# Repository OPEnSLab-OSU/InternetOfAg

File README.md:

# Project Loom: Library Overview

This is the primary location of the Project Loom code, consolidated into place with a single Arduino .ino sketch built with code selected by the preprocessor based on the configuration file. 

Other readmes are provided for more specific content, while this document focuses on providing an overview of what Loom is and how the library works.

#### Additional Readmes

- [Arduino and Loom Setup](https://github.com/OPEnSLab-OSU/InternetOfAg/tree/master/Arduino_and_Loom_Setup) – How to setup Arduino and Loom from scratch
- [Hardware](https://github.com/OPEnSLab-OSU/InternetOfAg/blob/master/Readme_Hardware.md) – The processors, sensors, actuators, etc. that Loom uses / supports 
- [Using Loom](https://github.com/OPEnSLab-OSU/InternetOfAg/blob/master/ReadMe_Using_Loom.md) – How to use Loom once you have set it and the Arduino IDE up
- [Extending Loom](https://github.com/OPEnSLab-OSU/InternetOfAg/blob/master/ReadMe_Extending_Loom.md) – How to add support to the Loom Library
- [Hub Scripts](https://github.com/OPEnSLab-OSU/InternetOfAg/blob/master/ReadMe_Hub_Scripts.md) – Documentation on the mini programs / scripts that Loom supports
- [Loom Translator](https://github.com/OPEnSLab-OSU/InternetOfAg/blob/master/ReadMe_Loom_Translator.md) – Documentation on the collection of Loom functions for converting between data types and organization
- [Max MSP](https://github.com/OPEnSLab-OSU/Loom-Max) – Details on using Max MSP data processors with WiFi enabled Loom devices
- [Limitations and Bugs](https://github.com/OPEnSLab-OSU/InternetOfAg/blob/master/Readme_Limitations_and_Bugs.md) – The processors, sensors, actuators, etc. that Loom uses / supports 

## Table of Contents

1. [Installation](#installation)

2. [Device Support](#device-support)

3. [Communication Platforms](#communication-platforms)

    1. [Notes on Internet Connectivity](#notes-on-internet-connectivity)

4. [Device Configuration](#device-configuration)

5. [Max/MSP](#max/msp)

6. [Library Architecture](#library-architecture)

    1. [Overall Structure](#overall-structure)
        1. [Example Library Include Hierarchy](#example-library-include-hierarchy)

7. [Channels](#channels)
    1. [Implementation](#implementation)
    2. [Additional Devices](#additional-devices)

8. [Device Identification Hierarchy](#device-identification-hierarchy)

9. [SD Card Support](#sd-card-support)

10. [Real-Time Clock Support](#real-time-clock-support)

11. [Non-Volatile Flash and EEPROM memory](#non-volatile-memory)

12. [Configuration File](#configuration-file)

13. [API](#api)

14. [Using the Loom Library](#using-the-loom-library)

## Installation

See our [Arduino and Loom Setup Guide](https://github.com/OPEnSLab-OSU/InternetOfAg/tree/master/Arduino_and_Loom_Setup)

## Device Support

- Adafruit Feather M0
- Adafruit Feather 32u4 *(limited support)*

## Communication Platforms

WiFi and LoRa have had the most attention in development and thus have the most support and options, especially WiFi, as that is currently the only to communicate with a computer running Max/MSP. Other platforms have been implemented however. Below is the table of device inputs and outputs currently implemented, planned, or in consideration (bold for well implemented, * if partially implemented or in need of testing to be considered well implemented, plaintext if planned but not implemented, ? if in consideration). The top section is device-device communication platforms, and the bottom section are platforms that do not necessarily transmit directly to another Loom device

| Inputs         | Outputs                     | Comments                                                     |
| -------------- | --------------------------- | ------------------------------------------------------------ |
| **WiFi**       | **WiFi**                    | Implemented                                                  |
| **LoRa**       | **LoRa**                    | Implemented                                                  |
| **nRF**        | **nRF**                     | Implemented                                                  |
| Ethernet       | Ethernet*                   | Currently only used with hubs, expansion in progress         |
| GSM            | GSM*                        | Currently only one device, so outputs MQTT via GSM, but no GSM receiving yet |
|                |                             |                                                              |
| Google Sheets? | Google Sheets (PushingBox)* | Works as output                                              |
| Adafruit IO*   | Adafruit IO*                | Needs proper integration                                     |
| IFTTT?         | IFTTT?                      | IFTTT currently only works as output though Adafruit IO      |
| SD card?       | **SD card**                 | Works as output, considering as input                        |
| Serial?        | **Serial**                  | Works for output. Serial as input may or may not be useful (is how Fona is tested) |
|                | **OLED**                    | Display a bundle on an Adafruit OLED featherwing / breakout  |

### Notes on Internet Connectivity

**Ethernet MAC Addresses:** 

If you are not on a network where MAC addresses are managed / locked if not explicitly approved, then you will need obtain a valid MAC address from your IT department. Once you have a MAC address, it can be set in the code with something like `byte mac[] = {0x98, 0x76, 0xB6, 0x10, 0x61, 0xD6};` It would generally be worth testing a new MAC address in basic example code first to ensure that will in fact work.

**WiFi Network Connectivity:** 

Many institutional / company WiFi network require a user's credentials to be access (rather than just network SSID and password). We do not currently support connecting to such networks, and it is unclear if this can be implemented on Arduinos at all.

As such, you can operated the Loom WiFi device in:

- Access point mode without internet access
- Client mode connected to a WiFi router that does not connect to an institutional/ username protected network for internet access
- Client mode connected to a WiFi router unconnected to internet for local communication between devices but no internet access

## Device Configuration

The configuration of the code to upload and flash to devices is specified in the config.h file. This file presents the options that can be set or toggled to achieve a particular behavior. The preprocessor uses these definitions to select the necessary declarations, variables, and functions automatically. 

Currently changes to the config need to be done manually in the file itself. An interface to aid the process is in progress.

## Max/MSP

The associated [Loom Data Processors](https://github.com/OPEnSLab-OSU/Loom-Max) and control modules are made as patches in Max/MSP. The Max interfaces are not strictly necessary for using this library, but provide convenient features and means of interacting with your Loom devices / network.

## Librarary Architecture

The Loom Library is an answer to the growing set of code to drive Loom's supported devices, hardware, and communication platforms. The set of possible combinations of device configurations makes it unfeasable for Loom developers and users alike to manage sketches with desired functionality. Instead, a configuration file effectively creates the desired sketch dynamically. A loom_preamble.h file uses that configuration to select entire files to include, each of which may also contain additional preprocessor statements.

### Overall Structure

The Loom Library is effectively an aggregate of all of the functionality possible within the entirety of the supported devices, sensors, and actuators. The user then specifies the needs of their sketch inside the `config.h`. Based on the needs of the sketch, the requisite files, functions, and logic will be dynamically included such that only what is needed by the sketch is uploaded to the device. loom_preamble.h uses `config.h` to know which files to include, these files in turn then include the libraries they need. `loom_common.h` is also always present as it has the `Loom_begin()` function, which sets up all the modules and sensors being used by the sketch. 

#### Example Library Include Hierarchy

The hierarchy of included files looks something like the following (example if building for Ishield device on Feather M0 WiFi)  *(actual files may have since changed, but the idea/hierarchy remain)*. 

**Note** – bolded are files that are always necessary and thus included, independent of `config.h`. In angle brackets are non-Loom dependencies.

- Ishield_Example.ino
  - **Config.h**
  - **Loom_preamble.h** (likely to be renamed)
    - **<OSCBundle.h>**
    - Loom_translator.h
    - <Adafruit_SleepyDog.h>
    - <SPI.h>
    - loom_analog.h
    - loom_neopixel.h
      - <Adafruit_NeoPixel.h>
    - loom_mpu6050.h
      - <I2Cdev.h>
      - <Wire.h>
      - <MPU6050_6Axis_MotionApps20.h>
    - loom_wifi.h
      - <WiFi101.h>
      - <WiFiUDP.h>
    - **loom_flash.h**
      - <FlashStorage.h>
    - **loom_common.h**

### Message Router

#### Intro to Route and Dispatch of Message Router

The message router is called via:

```
bndl->route(configuration.packet_header_string, msg_router);
```

From the `process_bundle` function in the 'loom_interface.h' file. The message router checks any OSC messages that it receives, and if the message's address string matches one of the dispatch calls in the router, then the message gets forwarded to a function designed to handle / process messages with that address string. This usually entails reading the arguments to the message (which should be sent in an order / format known by the function that will handle the processing).

The dispatch calls in the message router take the following form:

```
msg.dispatch("/address", processing_function, addrOffset);
```

An example of a dispatch that takes a message that has an address of the device identifying string followed by "setID", and calls a function `set_instance_num` (which sets the device instance number) would be:

```
msg.dispatch("/SetID", set_instance_num, addrOffset);
```

The reason only the `/SetID` is provided and not something like `/LOOM/Ishield7/SetID` is because the aforementioned route function checks for message addressed to the device, which in this case is identified by `/LOOM/Ishield7`, and passes only the remaining part of the address to the message router. Messages that do not start with the device indentifying string are not sent to the message router.

## Channels

The LOOM library and associated Max/MSP processors are designed to use channel based interfaces by default. Channel interfaces abstract device instance number, UDP port, and IP address into a single letter A, B, C, … H. 

The channels are purely a user convenience, and the devices can operate without any notion of channels in the firmware and/or Max patches.

### Implementation
A common port is used for the communication of device settings in order to allow the Max patches to communicate with devices in a consistent manner if the instance number, UDP port, or IP (i.e. the channel information) address are unknown.

**Common Port:** 9440 

**Device Unique Channnel Data:** 9441 – 9448

Channel A:	Instance # = 1		UDP Port = 9441	

Channel B:	Instance # = 2		UDP Port = 9442

• • •

Channel H:	Instance # = 8		UDP Port = 9448

**IP Address:** Automatically assigned to devices by one's router. Max interfaces will automatically fetch IP address of selected device. If not using the channels feature implemented in the Loom Max interfaces, then Loom Debug mode may need to be enabled, or the user may need to add custom code, in order to obtain the device's IP address.

### Additional Devices

The Max interfaces presently support upto 8 concurrent channels, though the library itself poses no such restrictions and using custom Max interfaces can allow for the control of more devices.

## Device Identification Hierarchy

In Loom, a device is uniquely identified by 4 elements, from broad to precise identification:

- Family
- Family number
- Device type
- Device number

The OSC messages and bundles send to and from devices are address/signed with their ID string, in the following format:

`/<Family><Family-Num>/<Device-Type><Device-Num>/<the-rest-of-the-address>`

For example, Ishield 7 in the 3 'Loom' subnet would be:

`/Loom3/Ishield7`

**Family**

A family is generally a complete network of a given functionality under a single person or group.

**Family Number**

A family number is used to distinguish subnets between a family. This is typically used to seperate devices into groups by purpose, location, etc. In Max/MSP, you will generally only be observing a single subnet at a time. Family numbers should be 0 or greater.

**Device Type**

The Loom Library supports an autoname feature to try to name your device if it fits into a common hardware / functionality set. These include devices like Ishields, multiplexers, servo controllers, etc. and name the device accordingly. Alternatively, you can use custom names for your devices if you want. 

**Device Number / Channel**

A device number is used to distinguish the devices on the same subnet (family number) that have the same device type. Device numbers are sometimes also referred to as channels. Device numbers are expected to be between 1 and 8, inclusive (channels A-H).

### WiFi UDP Ports

If using WiFi, the family number and device number will determine the UDP ports that the device will expect messages from. The device will check and send on 3 ports, one for global messages, one for subnet, and one for device specific messages. The calculation of the specific ports are shown below. The reason for different ports fro various devices/purposes is to reduce the number of messages a device may recieve that were not intended for it.

### Device Targetting Scope

The message routing function of the Loom Library supports receiving messages addressed at a global, subnet, or device level. Max/MSP can send on any of the 3 formats as well.

**Global** 

Broadcast the OSC bundle to all devices. Those with the matching family name can see/react to the message. If using WiFi the message is sent on UDP port `9400`.

`/<Family>/<command>`

**Subnet**

Broadcast to a single subnet of a given family. Those with the matching family name and family number can see/react to the message. If using WiFi the message is sent on UDP port `9400+10*(family-num)`.

`/<Family><Family-Num>/<command>`

**Device**

Target a message at a single device, i.e. the one with the matching family, family number, device type, and device number. If using WiFi the message is sent on UDP port `9400+10*(family-num)+(device-num)`.

`/<Family><Family-Num>/<Device-Type><Device-Num>/<command`

### LoRa Subnet

Loom also supports subnets with LoRa. This is implemented by having the receiver check the source of the received OSC bundle (from the device identification address), and filter out unwanted bundles (i.e. empty them). 

The options are specified in the config.h file by `lora_subnet_scope`:

- 1: subnet
- 2: global/family
- 3: global only (not recommended)
- 4: any message. 

(use 2 if unsure)

These achieve a similar subnet structure that is produced with UDP ports on the WiFi boards.

## SD Card Support

The Loom library extends the Arduino SD library to have more features, mostly tailored towards using common data structures used by the library.

Namely, support for printing:

- Single elements (int, floats, c-strings, Strings)
- Arrays (ints, floats, c-strings, Strings)
- Bundles (single or multi-msg format)

Additionally, if used with MaxMSP, there is support for sending commands to enable / disable the logging of bundles the device receives (also works without Max).

## Real-Time Clock Support

The Loom library supports two RTC devices:

- [Adafruit DS3231](https://learn.adafruit.com/adafruit-ds3231-precision-rtc-breakout/)
- [Adafruit PCF8523](https://learn.adafruit.com/adafruit-adalogger-featherwing)

Currently, interrupts (for waking the microprocessor from sleep) are only supported via the DS3231, with the PCF8523 mostly being used in conjunction with an SD card (as Adafruit Adalogger featherwing has PCF8523 and SD card holder) to provide timestamps.

The Loom Library has support for both devices for returning strings of the date, time, or weekday. Additional timer functions are provided for the DS3231.

#### RTC and Low Power Dependencies

- [DS3231 Extended Library](https://github.com/FabioCuomo/FabioCuomo-DS3231)
- [Low Power Library](https://github.com/rocketscream/Low-Power)
- [Enable Interrupt](https://github.com/GreyGnome/EnableInterrupt)

**NOTE:** To use the DS3231 extended library with the Feather M0,
the following line must be added to `RTClibExtended.h`:

```cpp
#define _BV(bit) (1 << (bit))
```

#### Sleep Modes

Project Loom supports two sleep modes for the Feather M0 and one sleep mode for the Feather 32u4.
Here are some details on the various modes:

| Mode           | Supported board | Current Draw |
| -------------- | --------------- | ------------ |
| Idle\_2        | Feather M0      | ~5 mA        |
| Standby        | Feather M0      | ~0.7 mA      |
| SLEEP\_FOREVER | Feather 32U4    | Untested     |

#### Standby Operation

Due to some incompatibilities between Standby mode and falling interrupts, a very particular
scheme must be followed to use Standby mode on the Feather M0.  The following code is an
example of how standby mode can be set up on the M0 with a wakeup interrupt on pin 11:

``` cpp
void setup() {
    pinMode(11, INPUT_PULLUP);
    bool OperationFlag = false;
    delay(10000); //It's important to leave a delay so the board can more easily
                  //be reprogrammed
}

void loop() {
    if (OperationFlag) {

        // Whatever you want the board to do while awake goes here

        OperationFlag = false; //reset the flag
    }

    attachInterrupt(digitalPinToInterrupt(11), wake, LOW);

    LowPower.standby();
}

void wake() {
    OperationFlag = true;
    detachInterrupt(digitalPinToInterrupt(11)); //detach the interrupt in the ISR so that
                                                //multiple ISRs are not called
}
```

#### Setting the Time from the Internet

Loom supports setting the RTC time based on the time obtained from an NTP server.

#### UTC Time

Loom supports the usage of either local or UTC time.

## Non-Volatile Flash and EEPROM memory

For storing configurations, both the Feather M0 and the Feather 32u4 boards are capable of storing a
struct in non-volatile memory. The functions related to non-volatile memory can be found in loom_flash.h,
and are automatically compatible with your board. If you modify the contents of the configuration structure,
you can save them with write_non_volatile(). If you need to read from flash memory, you can read into the
configuration structure with read_non_volatile(). Do not excessively write, as each board supports about
~10000 flash writesin its lifetime; the cells in flash memory wear out over time.

## Configuration File

The configuration file is used in conjunction with preprocessor statements to build the specified sketch, with as small a program memory usage as possible. Any options that can be set or toggled, or any specification of hardware (e.g. sensors and actuators) being used occur in this config.h.

Any options for custom additions to the library should be added only to the configuration file.

The config.h file needs to be included before the library (via loom_preamble.h) itself, so that the configuration can be used to define the necessary subset of the library.

## API

*'[]'s are used to indicate arguments that are optional or specific to a given platform* 

- Receive Bundle `void receive_bundle(OSCBundle *bndl, CommPlatform platform)`
  - Receive a packet and put it in an OSC bundle if not already
  - CommPlatform options:
    - WIFI
    - LORA
    - NRF
- Process Bundle `void process_bundle(OSCBundle *bndl)`
  - Process a bundle (presumably recieved via recieve_bundle) by performing message routing on it 
- Measure Sensors `void measure_sensors()`
  - Measure any enabled sensors
- Package Data `void package_data(OSCBundle *send_bndl)`
  - Package measured data into an OSC bundle  
- Send Bundle `void send_bundle(OSCBundle *send_bndl, CommPlatform platform)` 
  - Send a bundle (presumably built via package_data) to another Loom device / MaxMSP
- Log Bundle `void log_bundle(OSCBundle *send_bndl, LogPlatform platform [,char* file])`
  - Export a bundle
  - Platform options
    - PUSHINGBOX (Google Sheets)
    - SDCARD (requires filename)
    - OLED
- Additional Loop Checks `void additional_loop_checks()`
  - Function to catch remaining functionality that is not contained by the rest of the API

Further details on using the API can be found [here](https://github.com/OPEnSLab-OSU/InternetOfAg/blob/master/ReadMe_Using_Loom.md)

## Using the Loom Library

Details on setting up Arduino IDE and Loom can be found [here](https://github.com/OPEnSLab-OSU/InternetOfAg/tree/master/Arduino_and_Loom_Setup)

Details on using Loom once setup (with examples) can be found [here](https://github.com/OPEnSLab-OSU/InternetOfAg/blob/master/ReadMe_Using_Loom.md)

####

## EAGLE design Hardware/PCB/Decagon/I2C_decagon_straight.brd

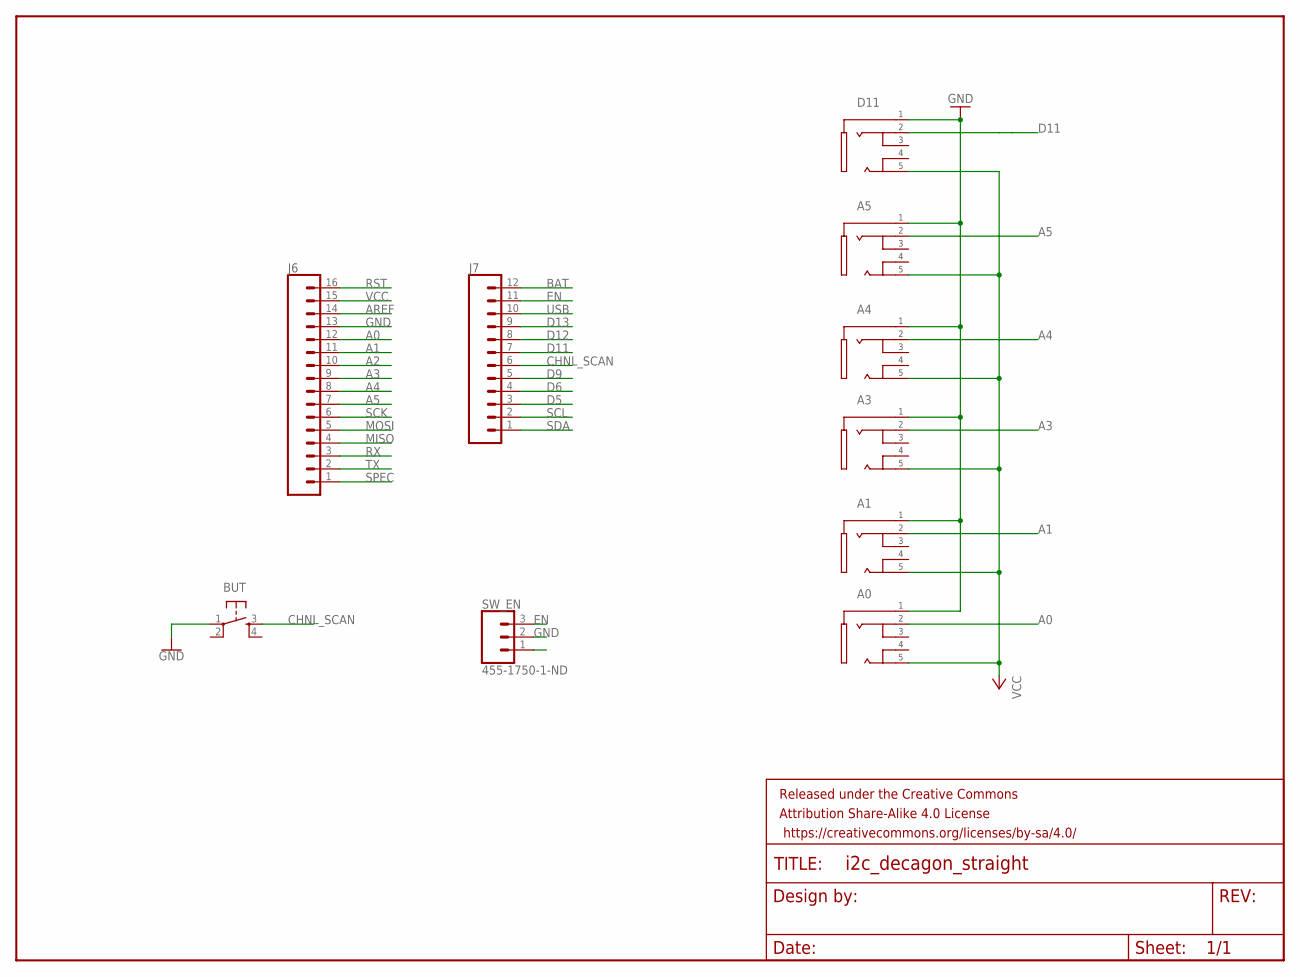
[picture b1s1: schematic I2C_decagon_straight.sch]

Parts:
A0, A1, A3, A4, A5: JW-PJ-307-5H
BUT: TAC_SWITCHPTH; TACTILE-PTH
D11: JW-PJ-307-5H
FRAME1: FRAME-LETTER; CREATIVE_COMMONS
J6: CONN_16; 1X16
J7: CONN_12; 1X12
SW_EN: 455-1750-1-ND; 1X03

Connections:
A0: A0.2, J6.12
A1: A1.2, J6.11
A2: J6.10
A3: A3.2, J6.9
A4: A4.2, J6.8
A5: A5.2, J6.7
AREF: J6.14
BAT: J7.12
CHNL_SCAN: BUT.3, J7.6
D5: J7.3
D6: J7.4
D9: J7.5
D11: D11.2, J7.7
D12: J7.8
D13: J7.9
EN: J7.11, SW_EN.3
GND: A0.1, A1.1, A3.1, A4.1, A5.1, BUT.1, D11.1, J6.13, SW_EN.2
MISO: J6.4
MOSI: J6.5
RST: J6.16
RX: J6.3
SCK: J6.6
SCL: J7.2
SDA: J7.1
SPEC: J6.1
TX: J6.2
USB: J7.10
VCC: A0.5, A1.5, A3.5, A4.5, A5.5, D11.5, J6.15

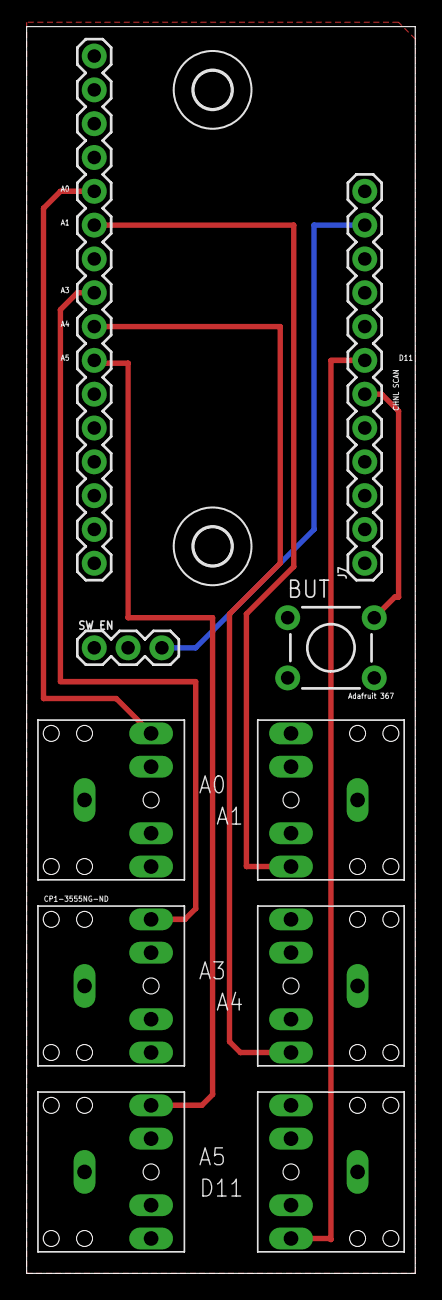
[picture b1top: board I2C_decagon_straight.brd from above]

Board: 2 copper layers, 29.2 x 93.7 mm, 13 parts (0 on the bottom side), 10 nets.

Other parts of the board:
U$1, U$2: 2,8

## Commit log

2017-11-29 Added Decagon soil moisture sensor demo
2017-11-30 Created subroutines for reading decagon values and sending OSC bundles
2018-01-17 Added Decagon functionality
2018-02-01 Added code to operate multiple decagon sensors
2018-02-07 Edited multiple decagon sensor code to be functional
2018-02-07 Changes for demo
2018-02-12 Modified OSC_interpret to account for messages with multiple data
2018-02-12 Added dynamic sensor polling on pins A0-A5
2018-02-16 Added sensor specific processing for GS3 and 5TM
2018-02-16 Added 32u4 compatibility
2018-02-16 32u4 changes
2018-02-22 Added 32u4 compatibility to nRF_OSCtransmit/receive
2018-02-28 Updated pins for 32u4 compatibility
2018-03-07 Interpretter revamp for multiple data values
2018-03-07 Servo code taking inputs in serial monitor
2018-03-07 OSCbundle+servo
    Applied OSCbundle library and etc to the servo code to use maxmsp
2018-03-10 Added PC application and LoRa OSC bundle send template
2018-03-10 Removed unnecessary library
2018-03-12 Quick receive edit for check off
2018-03-13 Added Decagon and Thermocouple code
2018-03-13 Added nRF code
2018-03-13 Added nRF thermocouple code
2018-03-13 Servo codes work with m0 and 32u4 through LoRa
    Servo_LoRa : Servo code
    LoRa_xransmit: transmitter code
2018-03-16 Added new files
2018-03-16 nrf data rate code added
2018-04-17 Code altered to allow larger bundles
2018-04-17 Readme update
2018-05-17 Removed RTC functionality for expo demo
2018-06-06 add static/dynamic i2c device configuration for mpu6050
2019-01-28 Fix Pushingbox readme to include tab ID in example format
2019-02-06 testing commitability
2019-02-06 Fixed archived libraries to be easier to use.
2019-02-15 Added turbidity conversion
2019-02-15 Restore .ino
2019-02-15 Added EC and TDS conversions
2019-02-22 Added Doxygen Make file for generating project documentation
2019-02-22 Readme edits
2019-02-22 Update dependencies folder
2019-02-27 Fix Ms5803 library to take i2c as parameter
2019-03-01 Minor Max31856 declaration rearrangement
2019-03-01 Remove old images folder
2019-03-01 Added BEE 222 instance
2019-03-22 New Decagon board
    Fixed order for snapping off unused ports. Change formfactor
2019-03-26 Fixed traces on Decagon 2.1
2019-04-01 Moved Traces clearance
2019-04-03 Traces shifted
    Modified 2.1 version to put more space between traces and soldering locations. Added silk screen text for relevant pins.
2019-05-03 Add Basic Sketch
2019-05-15 Commit pin ints code
2019-06-03 Fixed a stray ampersand that prevents compilation
    This damn ampersand keeps getting missed in pushes cause its an easy fix, so I'm ending this once and for all. Thou shalt not be a reference.
2019-06-04 Special version of Loom for Bee222
2019-06-04 Delete LOOM_library.ino
    Using an alternative .ino for this branch
2019-06-04 Added for timed functionality
2019-06-04 modified Loom_222Test to communicate with google sheets directly over SSL, need to troubleshoot OSU_Access
2019-06-04 Create PinInterrupts
2019-06-04 removed my wifi credentials and reset my password (whoops)
2019-06-13 Add EthernetLarge library
2019-06-14 fixed loom dependencies from inconsistent folder structure and missing libraries
2019-07-06 'final' version of code, seems to work as intended, readings taken every minute
2019-07-08 Fix annoying thermocouple enabled by default
2019-07-08 Changed options connected to data being read as well as sleep type
2019-07-08 Fix Pacific Daylight Time offset
2019-07-08 Medium hardness draft for final firmware, awaiting in lab testing to confirm deployment readiness
2019-07-17 Add new dependencies

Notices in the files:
parts and their libraries:
SparkFun-Retired: Licensing: Creative Commons ShareAlike 4.0 International - https://creativecommons.org/licenses/by-sa/4.0
SparkFun-Aesthetics: Released under the Creative Commons Attribution Share-Alike 4.0 License
SparkFun-Aesthetics: https://creativecommons.org/licenses/by-sa/4.0
